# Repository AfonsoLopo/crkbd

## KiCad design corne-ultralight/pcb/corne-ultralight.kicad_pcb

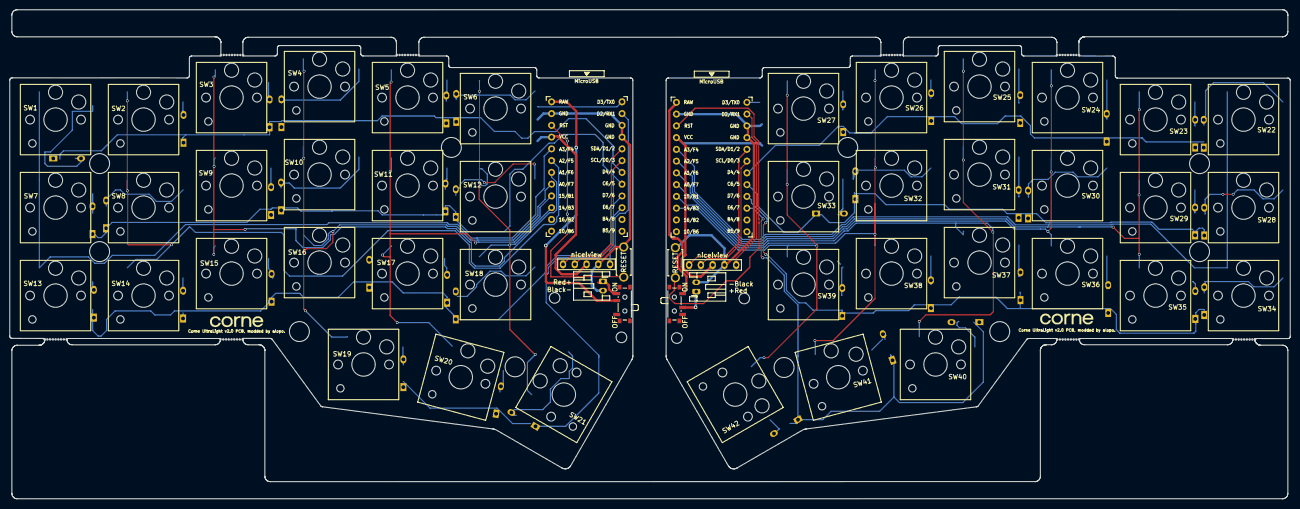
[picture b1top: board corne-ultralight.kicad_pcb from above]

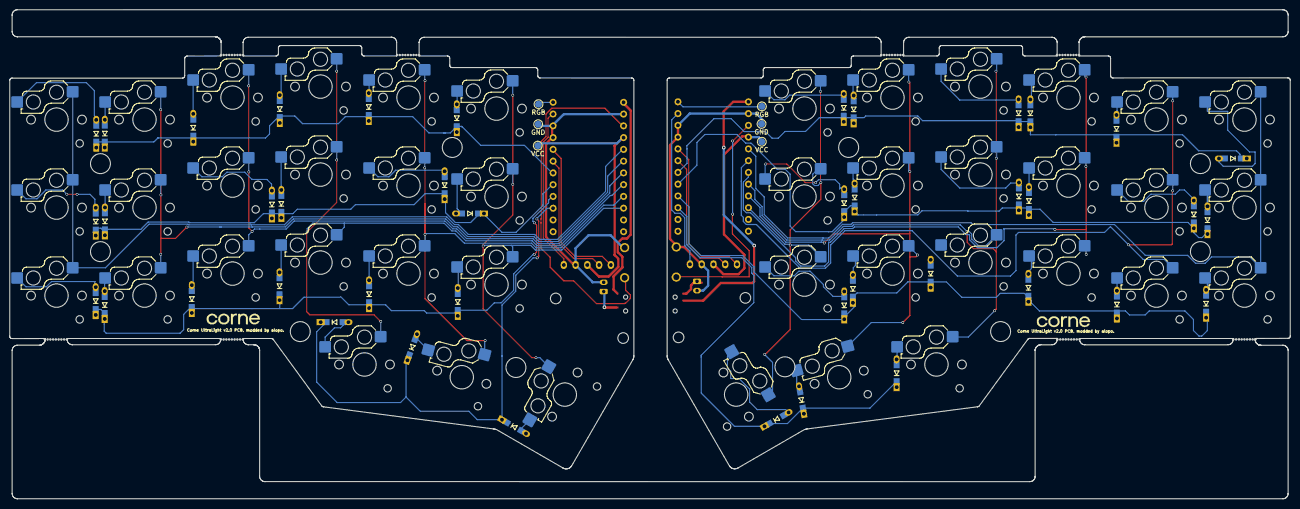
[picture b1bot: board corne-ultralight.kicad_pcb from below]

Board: 2 copper layers, 276.5 x 105.6 mm, 122 parts (60 on the bottom side), 45 nets.

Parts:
BATJ2, BATJ4: Conn_01x02_Female; JST_PH_S2B-PH-K_1x02_P2.00mm_Horizontal
D1, D2, D3, D4, D5, D6, D7, D8, D9, D10, D11, D12, D13, D14, D15, D16, D17, D18, D19, D20, D21, D22, D23, D24, D25, D26, D27, D28, D29, D30, D31, D32, D33, D34, D35, D36, D37, D38, D39, D40, D41, D42: D; D3_TH_SMD_v2
J2, J7: OLED; nice_view_1side
J5, J5#2, J5#3, J5#4, J5#5, J5#6, J5#7, J5#8: Breakaway_Tabs
PSW1, PSW2: SW_SPST; SW_SPDT_PCM12
RSW1, RSW2: SW_PUSH; ResetSW_1side
Ref**: Val**; thread_m2
Ref**#2, Ref**#8, Ref**#9: Val**; thread_m2
Ref**#3, Ref**#4, Ref**#5, Ref**#6, Ref**#7, Ref**#10, Ref**#11, Ref**#12, Ref**#13, Ref**#14: Val**; spacer_m2
SW1, SW2, SW3, SW4, SW5, SW6, SW7, SW8, SW9, SW10, SW11, SW12, SW13, SW14, SW15, SW16, SW17, SW18, SW19, SW20, SW22, SW23, SW24, SW25, SW26, SW27, SW28, SW29, SW30, SW31, SW32, SW33, SW34, SW35, SW36, SW37, SW38, SW39, SW40, SW41: SW_PUSH; Hotswap_Choc_V1V2_1.00u
SW21, SW42: SW_PUSH; Hotswap_Choc_V1V2_1.50u
TP1, TP4: RGB; TestPoint_Pad_D1.5mm
TP2, TP5: VCC; TestPoint_Pad_D1.5mm
TP3, TP6: GND; TestPoint_Pad_D1.5mm
U1, U2: ProMicro; ProMicro_v3

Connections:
+BATT: PSW1.2 (B), U1.24 (RAW)
+BATTA: PSW2.1 (A), U2.24 (RAW)
CS: J2.5, U1.2 (RX1/D2)
CS_r: J7.5, U2.2 (RX1/D2)
GND: BATJ2.2, J2.4, RSW1.2, TP3.1, U1.3 (GND), U1.4 (GND), U1.23 (GND)
GNDA: BATJ4.2, J7.4, RSW2.2, TP6.1, U2.3 (GND), U2.4 (GND), U2.23 (GND)
unnamed: BATJ2.1, PSW1.3 (C)
unnamed: BATJ4.1, PSW2.2 (B)
unnamed: D3.2 (A), SW3.2
unnamed: D4.2 (A), SW4.2
unnamed: D5.2 (A), SW5.2
unnamed: D11.2 (A), SW11.2
unnamed: D19.2 (A), SW19.2
unnamed: D20.2 (A), SW20.2
unnamed: D21.2 (A), SW21.2
RGB: TP1.1, U1.1 (TX0/D3)
RGB_r: TP4.1, U2.1 (TX0/D3)
SCL: J2.2, U1.6 (3/D0/SCL)
SCL_r: J7.2, U2.6 (3/D0/SCL)
SDA: J2.1, U1.5 (2/D1/SDA)
SDA_r: J7.1, U2.5 (2/D1/SDA)
VCC: J2.3, TP2.1, U1.21 (VCC)
VDD: J7.3, TP5.1, U2.21 (VCC)
col0: SW1.1, SW7.1, SW13.1, U1.20 (F4/A3)
col0_r: SW22.1, SW28.1, SW34.1, U2.20 (F4/A3)
col1: SW2.1, SW8.1, SW14.1, U1.19 (F5/A2)
col1_r: SW23.1, SW29.1, SW35.1, U2.19 (F5/A2)
col2: SW3.1, SW9.1, SW15.1, U1.18 (F6/A1)
col2_r: SW24.1, SW30.1, SW36.1, U2.18 (F6/A1)
col3: SW4.1, SW10.1, SW16.1, SW19.1, U1.17 (F7/A0)
col3_r: SW25.1, SW31.1, SW37.1, SW40.1, U2.17 (F7/A0)
col4: SW5.1, SW11.1, SW17.1, SW20.1, U1.16 (B1/15)
col4_r: SW26.1, SW32.1, SW38.1, SW41.1, U2.16 (B1/15)
col5: SW6.1, SW12.1, SW18.1, SW21.1, U1.15 (B3/14)
col5_r: SW27.1, SW33.1, SW39.1, SW42.1, U2.15 (B3/14)
reset: RSW1.1, U1.22 (RST)
reset_r: RSW2.1, U2.22 (RST)
row0: D1.1 (K), D2.1 (K), D3.1 (K), D4.1 (K), D5.1 (K), D6.1 (K), U1.7 (4/D4)
row0_r: D22.1 (K), D23.1 (K), D24.1 (K), D25.1 (K), D26.1 (K), D27.1 (K), U2.7 (4/D4)
row1: D7.1 (K), D8.1 (K), D9.1 (K), D10.1 (K), D11.1 (K), D12.1 (K), U1.8 (5/C6)
row1_r: D28.1 (K), D29.1 (K), D30.1 (K), D31.1 (K), D32.1 (K), D33.1 (K), U2.8 (5/C6)
row2: D13.1 (K), D14.1 (K), D15.1 (K), D16.1 (K), D17.1 (K), D18.1 (K), U1.9 (6/D7)
row2_r: D34.1 (K), D35.1 (K), D36.1 (K), D37.1 (K), D38.1 (K), D39.1 (K), U2.9 (6/D7)
row3: D19.1 (K), D20.1 (K), D21.1 (K), U1.10 (7/E6)
row3_r: D40.1 (K), D41.1 (K), D42.1 (K), U2.10 (7/E6)

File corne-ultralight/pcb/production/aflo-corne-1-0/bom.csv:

Designator,Footprint,Quantity,Value,LCSC Part #
"BATJ2, BATJ4",JST_PH_S2B-PH-K_1x02_P2.00mm_Horizontal,2,Conn_01x02_Female,
"D1, D10, D11, D12, D13, D14, D15, D16, D17, D18, D19, D2, D20, D21, D22, D23, D24, D25, D26, D27, D28, D29, D3, D30, D31, D32, D33, D34, D35, D36, D37, D38, D39, D4, D40, D41, D42, D5, D6, D7, D8, D9",D3_TH_SMD_v2,42,D,
"J2, J7",nice_view_1side,2,OLED,
"J5_8, J5_7, J5_6, J5_5, J5_4, J5_3, J5_2, J5",Breakaway_Tabs,8,Breakaway_Tabs,
"PSW1, PSW2",SW_SPDT_PCM12,2,SW_SPST,
"RSW1, RSW2",ResetSW_1side,2,SW_PUSH,
"SW1, SW10, SW11, SW12, SW13, SW14, SW15, SW16, SW17, SW18, SW19, SW2, SW20, SW22, SW23, SW24, SW25, SW26, SW27, SW28, SW29, SW3, SW30, SW31, SW32, SW33, SW34, SW35, SW36, SW37, SW38, SW39, SW4, SW40, SW41, SW5, SW6, SW7, SW8, SW9",Hotswap_Choc_V1V2_1.00u,40,SW_PUSH,
"SW21, SW42",Hotswap_Choc_V1V2_1.50u,2,SW_PUSH,
"TP1, TP4",TestPoint_Pad_D1.5mm,2,RGB,
"TP2, TP5",TestPoint_Pad_D1.5mm,2,VCC,
"TP3, TP6",TestPoint_Pad_D1.5mm,2,GND,
"U1, U2",ProMicro_v3,2,ProMicro,

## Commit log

2024-02-24 Mods to Ultra Light crkbd
